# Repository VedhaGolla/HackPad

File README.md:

# Forget-me-not Hackpad
## Inspiration:

As a Powerless trilogy fan and an admirer of flowers, I wanted to make a hackpad for my computer. The objective of this hackpad is to be a shortcuts mini keyboard that everyone uses almost daily! I also wanted to incorporate an important flower from my favourite book series of all time, the forget-me-not. This hackpad also has an inspirational quote from the book series. It is both a useful daily mini keyboard and an inspirational little piece. 

## Challenges:

Figuring out the CAD measurements and the PCB editor was difficult. The firmware was also quite difficult to understand. 
The timeline was also a little tight because I wanted to submit as soon as more hackpad submissions opened up. 

## Technical Features:
### Top row buttons: 
Copy, Paste, Screenshot

### Bottom row buttons:
Switch Window (Alt+Tab), Close Tab

### Rotary Encoder 1:
Rotate clockwise → Volume Up, Rotate counterclockwise → Volume Down, Press encoder → Mute

### Rotary Encoder 2:
Rotate clockwise → Scroll Down, Rotate counterclockwise → Scroll Up, Press encoder  → Play/Pause 

## CAD model:

## Schematic:

## PCB design:

## BOM:

| Qty | Item | Notes |
|---|---|---|
| 1 | Seeed XIAO RP2040 | Unsoldered |
| 5 | MX-style switches | |
| 2 | EC11 rotary encoders | |
| 5 | DSA keycaps | White, blank |
| 6 | M3 x 16mm screws | |
| 6 | M3 x 5mm x 4mm heatset inserts | |

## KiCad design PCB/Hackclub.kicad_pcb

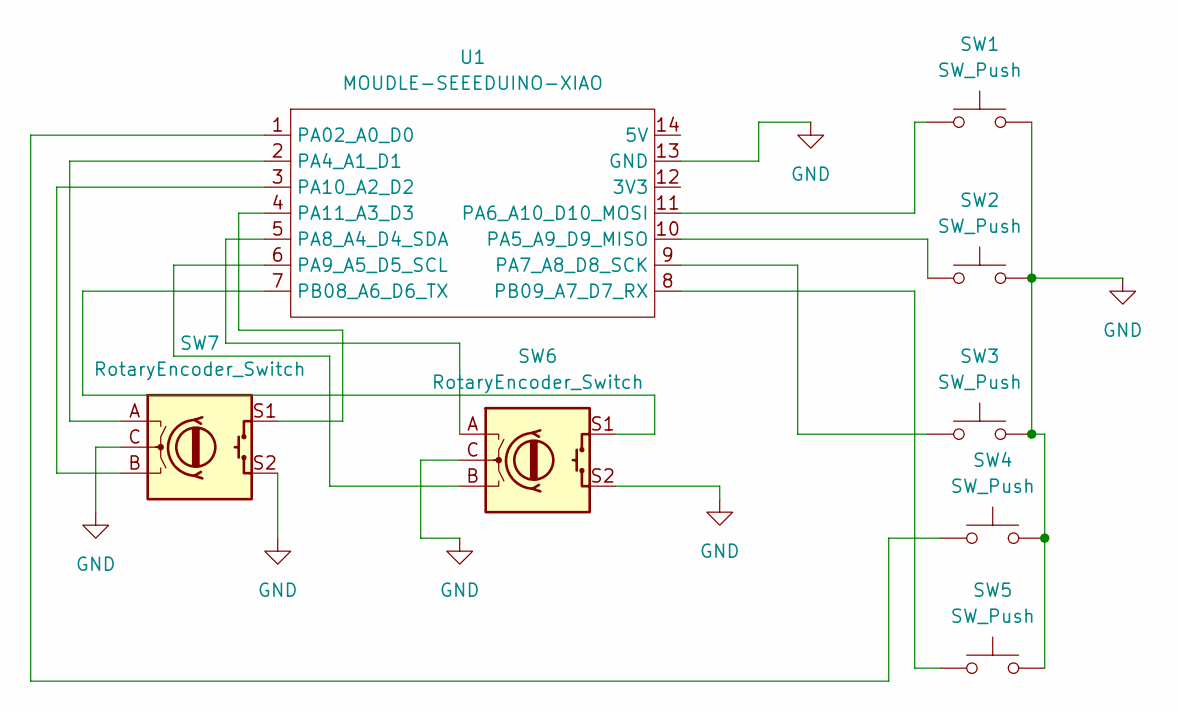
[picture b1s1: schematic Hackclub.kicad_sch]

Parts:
SW1, SW2, SW3, SW4, SW5: SW_Push; SW_Cherry_MX_1.00u_PCB
SW6, SW7: RotaryEncoder_Switch; RotaryEncoder_Alps_EC11E-Switch_Vertical_H20mm_MountingHoles
U1: MOUDLE-SEEEDUINO-XIAO; XIAO-Generic-Hybrid-14P-2.54-21X17.8MM

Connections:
GND: SW1.2, SW2.2, SW3.2, SW4.2, SW5.2, SW6.C, SW6.S2, SW7.C, SW7.S2, U1.13 (GND)
unnamed: SW4.1, U1.1 (PA02_A0_D0)
unnamed: SW7.A, U1.2 (PA4_A1_D1)
unnamed: SW2.1, U1.10 (PA5_A9_D9_MISO)
unnamed: SW1.1, U1.11 (PA6_A10_D10_MOSI)
unnamed: SW3.1, U1.9 (PA7_A8_D8_SCK)
unnamed: SW6.A, U1.5 (PA8_A4_D4_SDA)
unnamed: SW6.B, U1.6 (PA9_A5_D5_SCL)
unnamed: SW7.B, U1.3 (PA10_A2_D2)
unnamed: SW7.S1, U1.4 (PA11_A3_D3)
unnamed: SW6.S1, U1.7 (PB08_A6_D6_TX)
unnamed: SW5.1, U1.8 (PB09_A7_D7_RX)

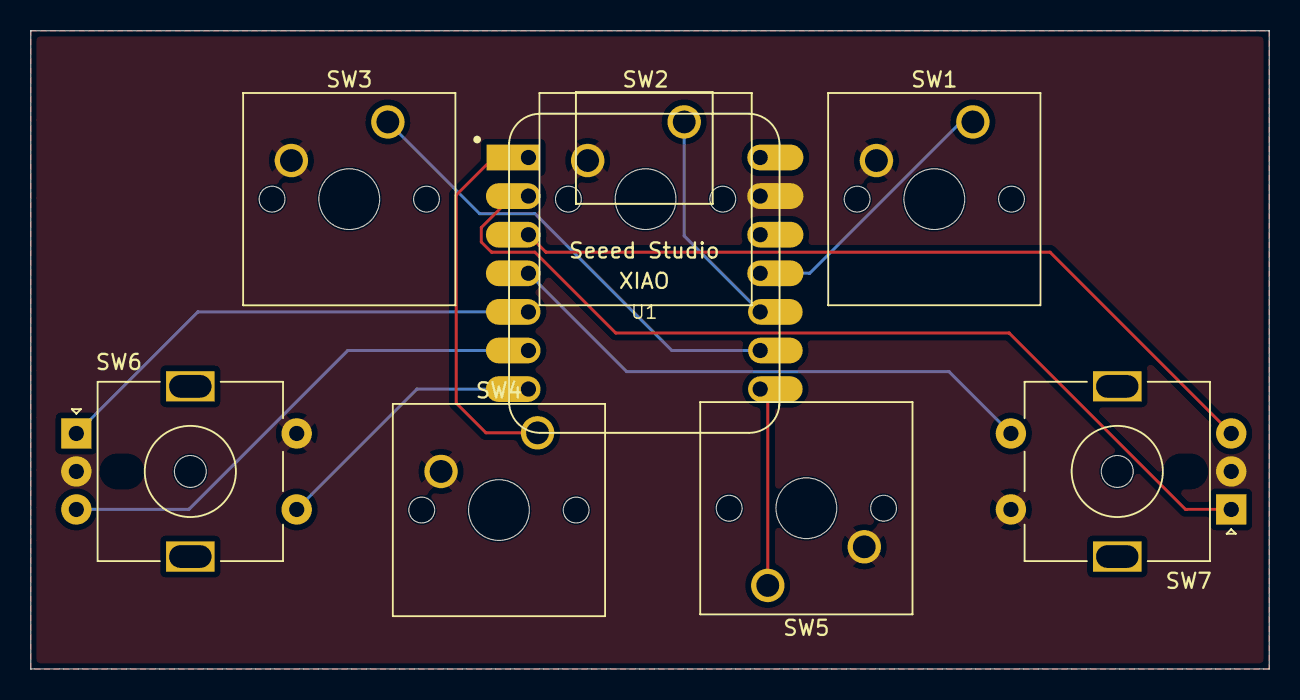
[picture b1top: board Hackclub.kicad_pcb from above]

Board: 2 copper layers, 81.5 x 42.0 mm, 8 parts (0 on the bottom side), 12 nets.
